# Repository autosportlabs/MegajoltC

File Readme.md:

Megajolt/C hardware and firmware

Project is incomplete. No support offered - github issues will be ignored. 

Please see LICENSE file for license details

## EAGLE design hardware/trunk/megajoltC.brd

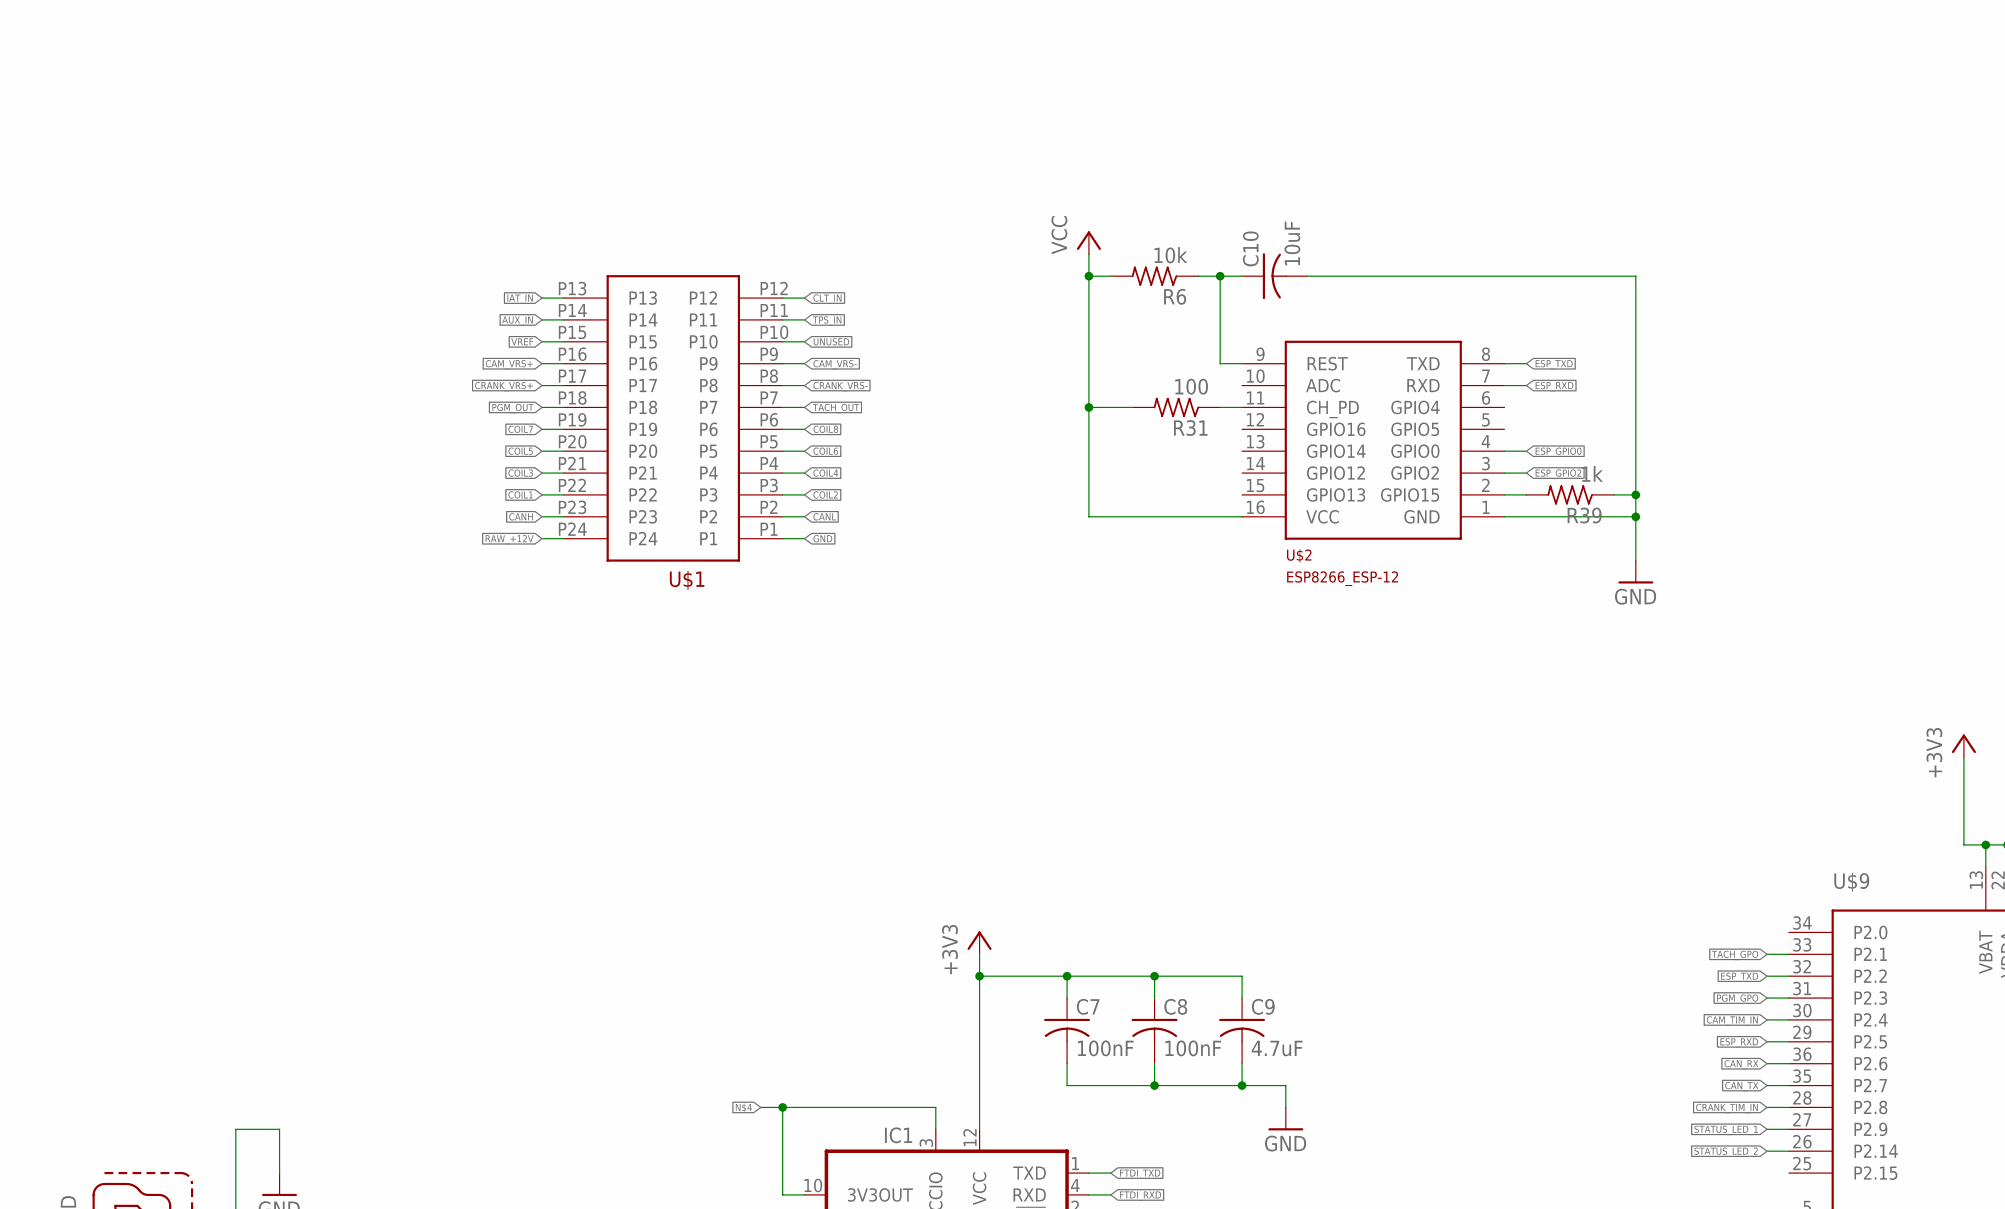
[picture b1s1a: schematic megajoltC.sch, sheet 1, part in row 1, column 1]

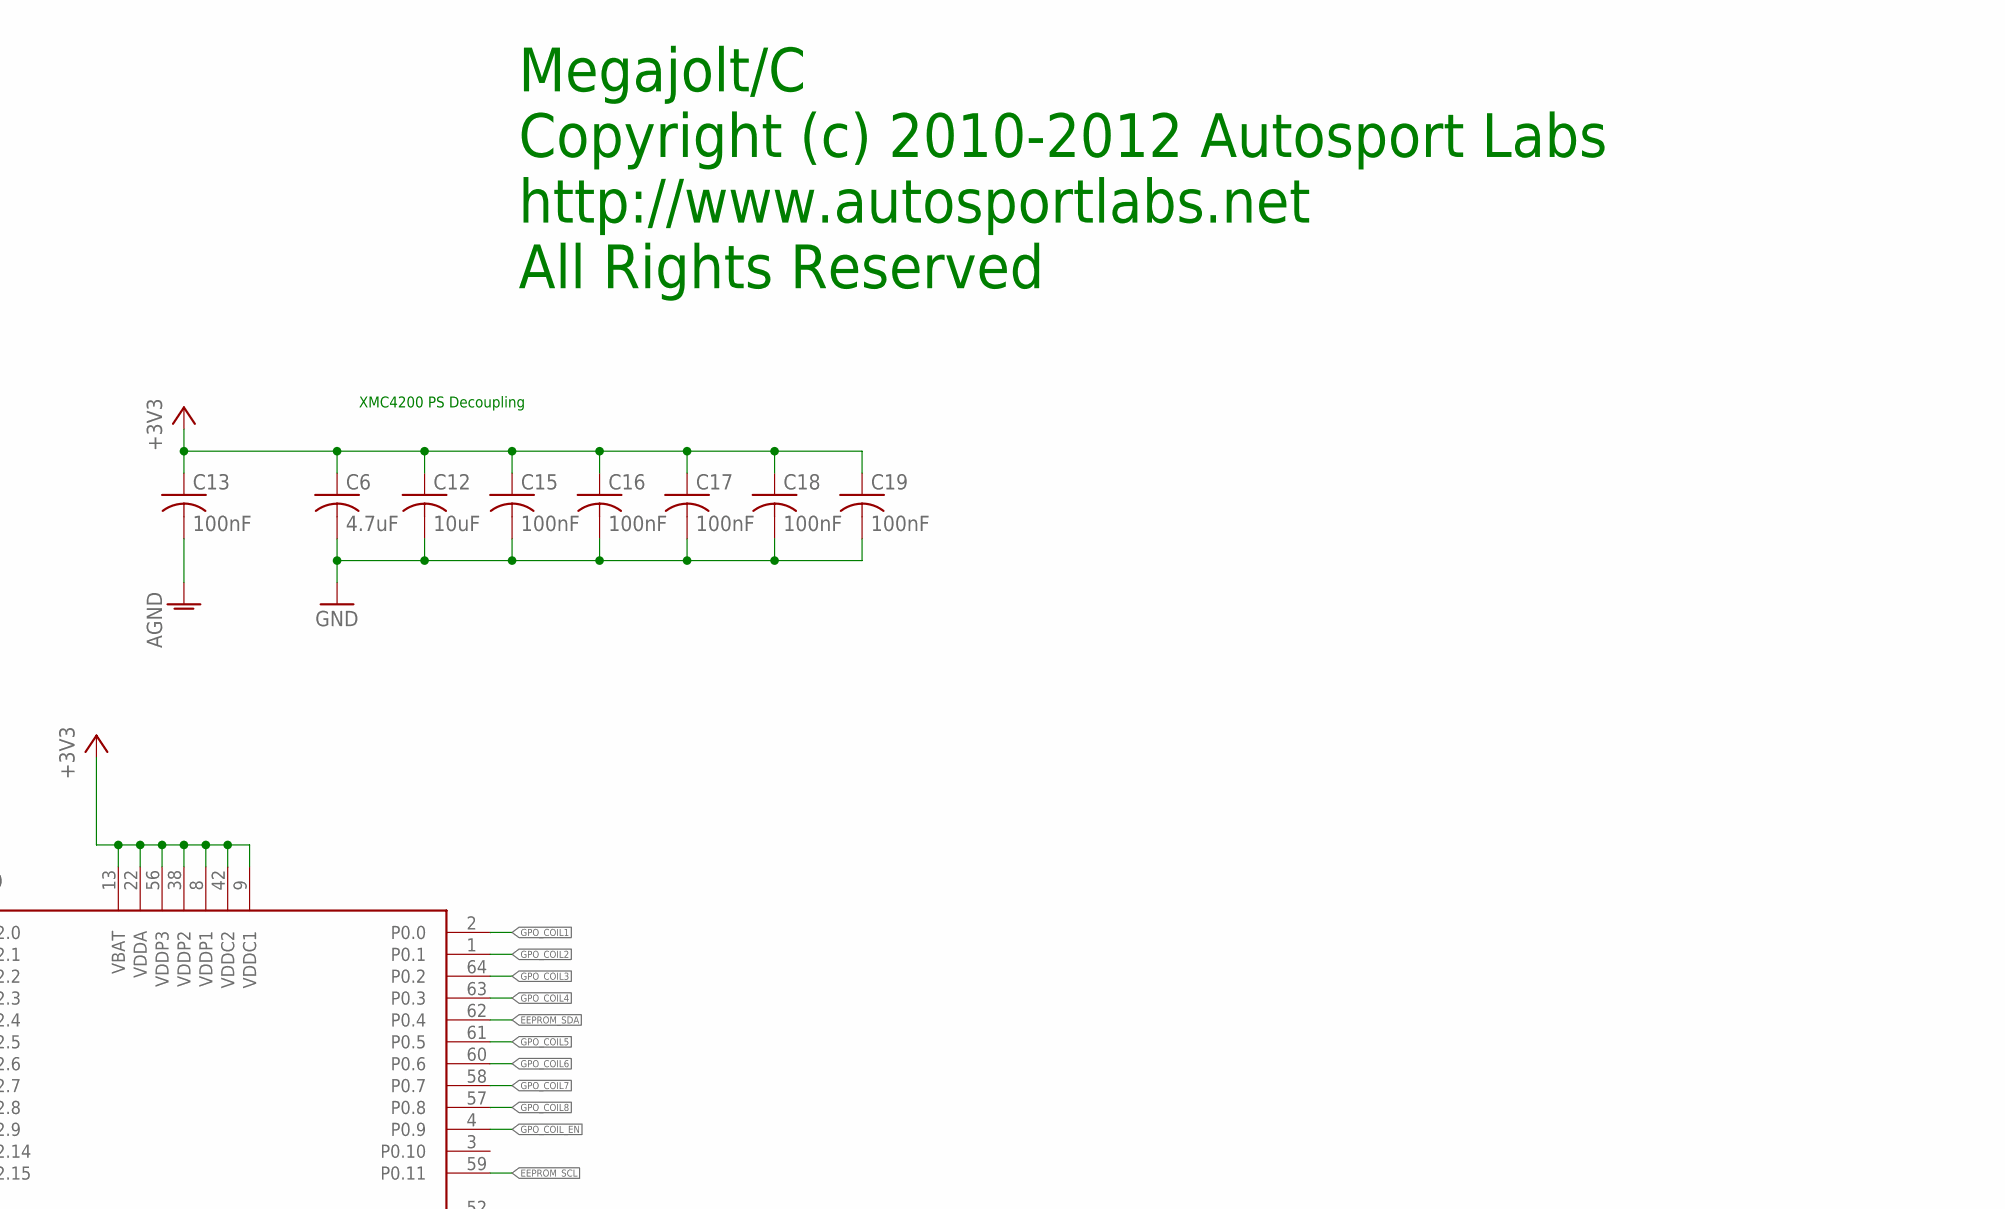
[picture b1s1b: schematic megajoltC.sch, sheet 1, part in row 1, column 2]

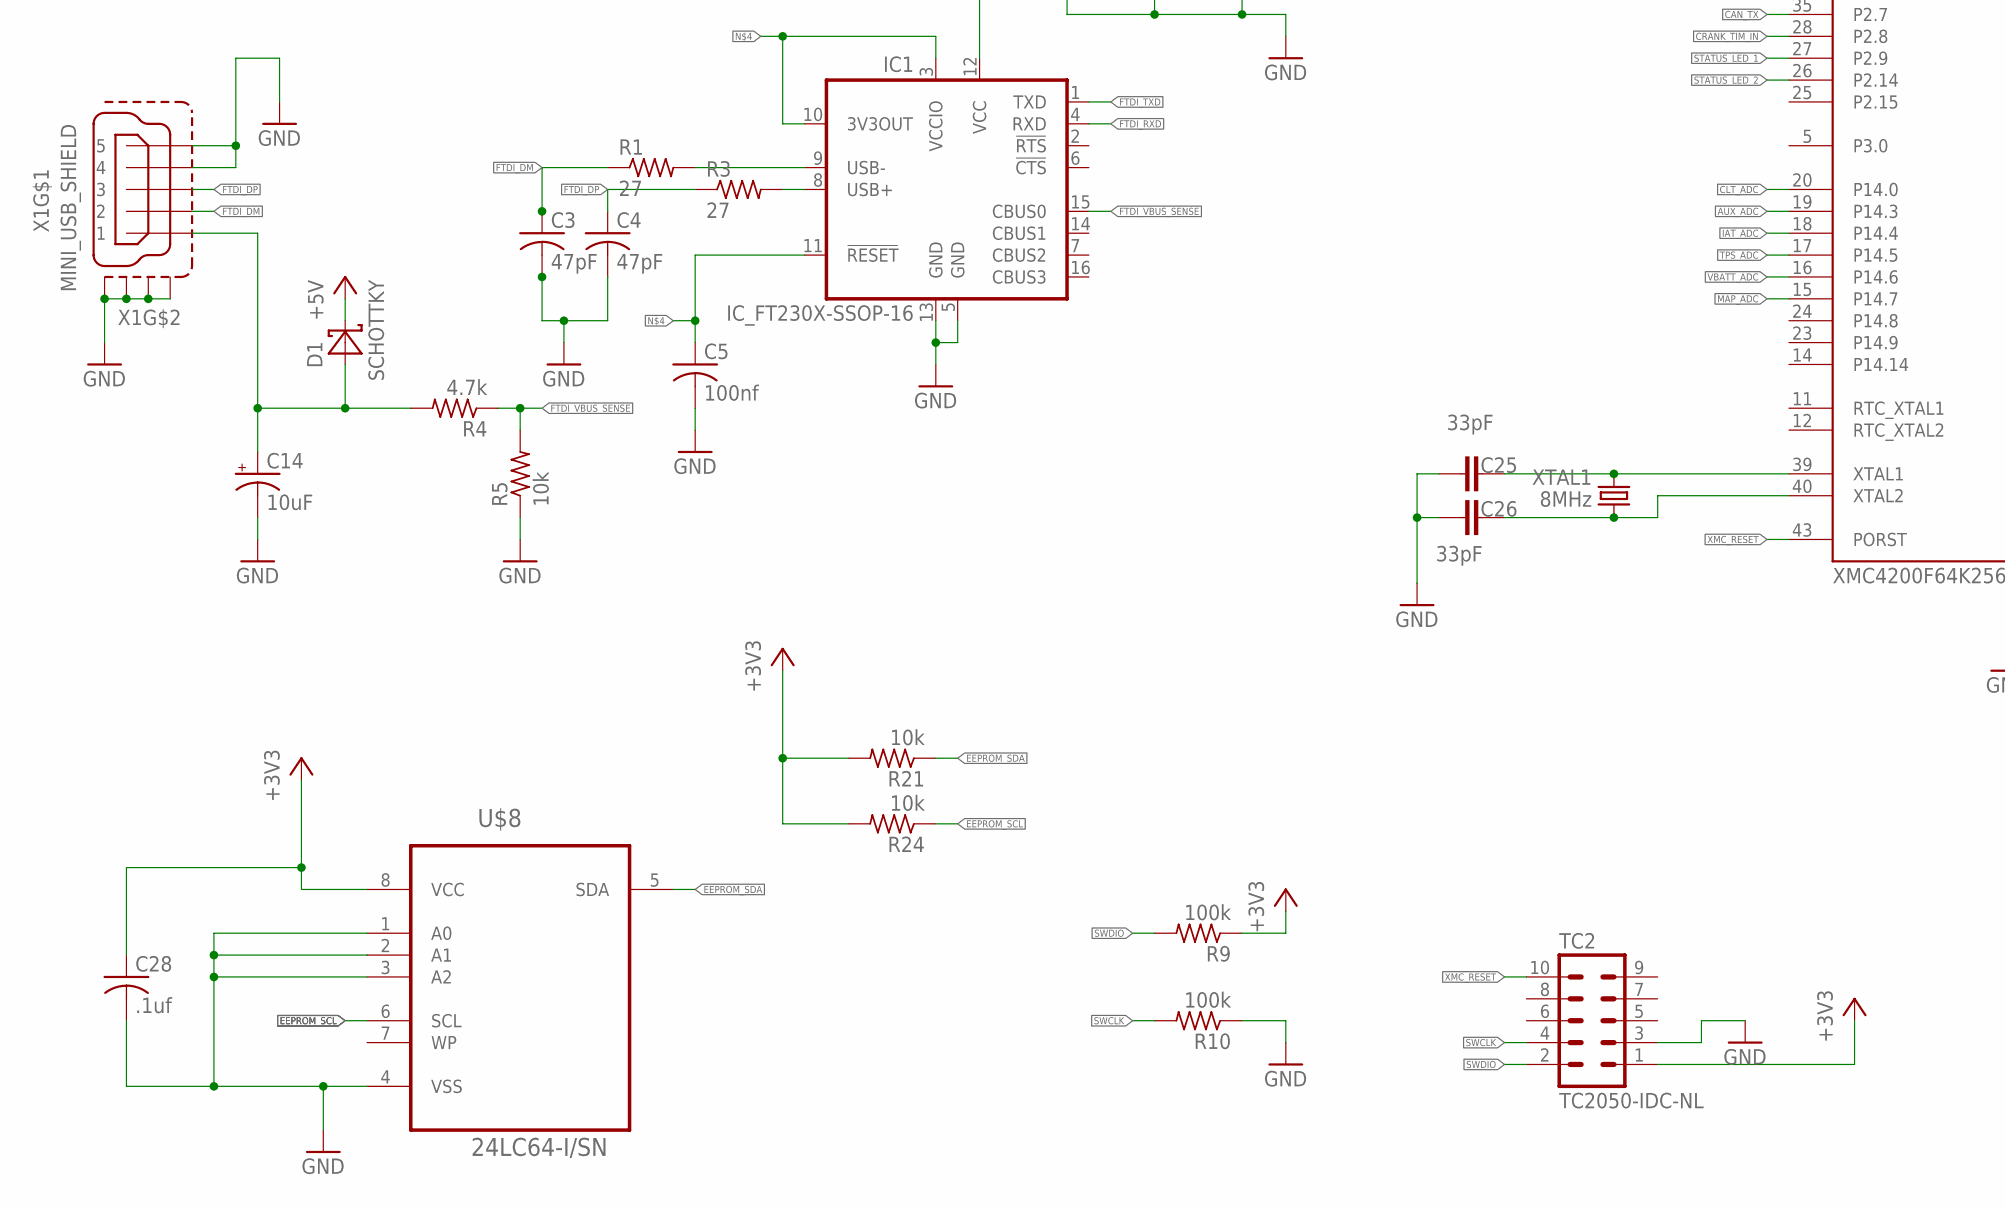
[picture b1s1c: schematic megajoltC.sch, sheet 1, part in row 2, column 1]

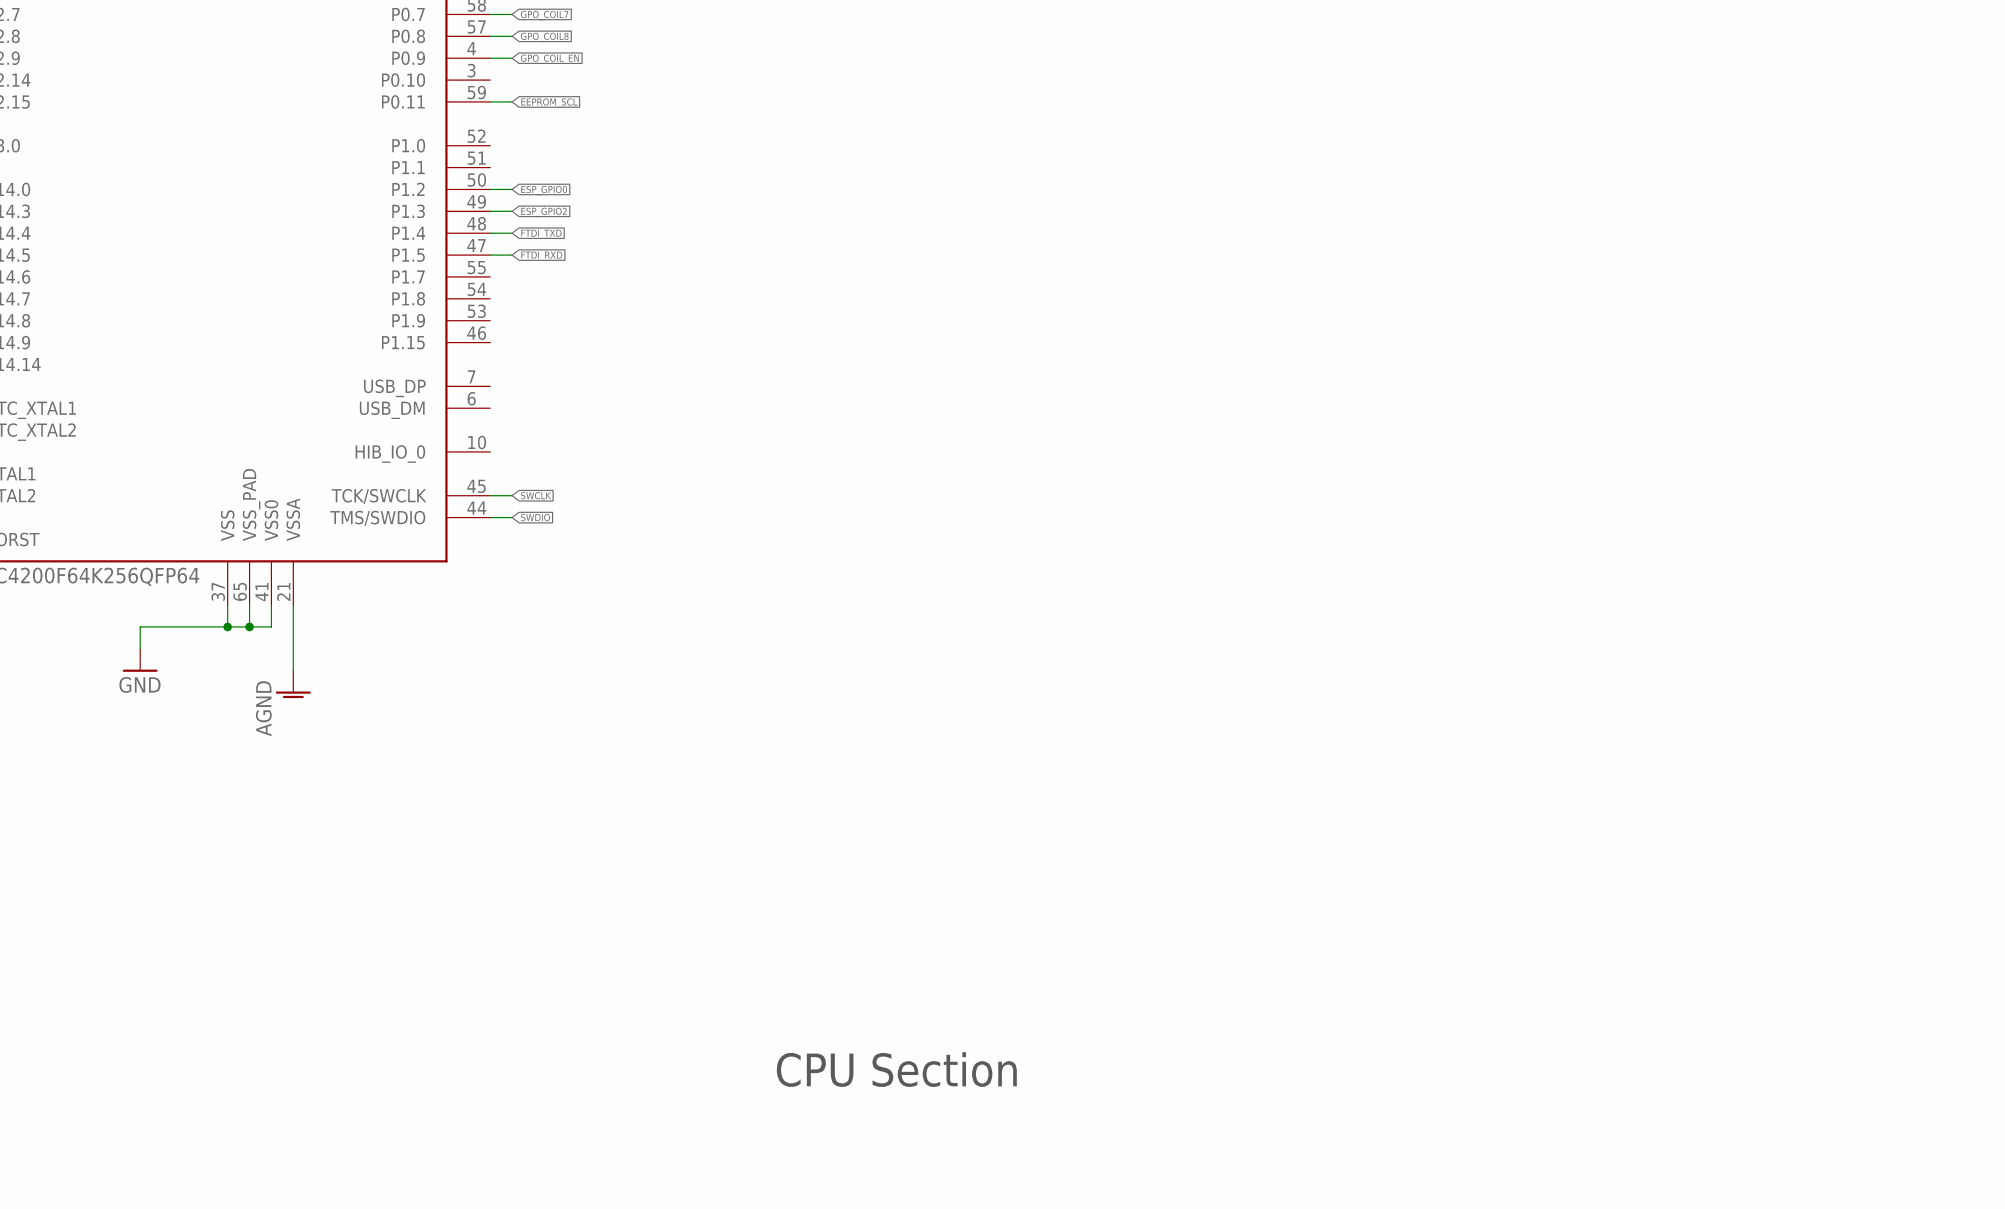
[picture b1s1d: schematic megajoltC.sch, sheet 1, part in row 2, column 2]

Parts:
C3, C4: 47pF; C0603
C5: 100nf; C0603
C6, C9: 4.7uF; C0603
C7, C8, C13, C15, C16, C17, C18, C19: 100nF; C0603
C10, C12: 10uF; C0603
C14: 10uF; SMC_A
C25, C26: 33pF; 0603
C28: .1uf; C0603
D1: SCHOTTKY; SMA
IC1: IC_FT230X-SSOP-16; SSOP-16-FTDI
R1, R3: 27; R0603
R4: 4.7k; R0603
R5, R6, R21, R24: 10k; R0603
R9, R10: 100k; R0603
R31: 100; R0603
R39: 1k; R0603
TC2: TC2050-IDC-NL
U$1: MOLEX_MINIFIT-JR-24
U$2: ESP8266_ESP-12; ESP8266-ESP12
U$8: 24LC64-I/SN; SOIC127P600X175-8N
U$9: XMC4200F64K256QFP64; INF-PG-LQFP-64-5800X5800T28
X1: MINI_USB_SHIELD; MINI-USB_JACK
XTAL1: 8MHz; CRYSTAL-SMD-5X3

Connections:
+3V3: C6.1, C7.1, C8.1, C9.1, C12.1, C13.1, C15.1, C16.1, C17.1, C18.1, C19.1, C28.1, IC1.12 (VCC), R9.1, R21.2, R24.2, TC2.1, U$8.8 (VCC), U$9.8 (VDDP1), U$9.9 (VDDC1), U$9.13 (VBAT), U$9.22 (VDDA), U$9.38 (VDDP2), U$9.42 (VDDC2), U$9.56 (VDDP3); also elsewhere on the board
+5V: D1.C; also elsewhere on the board
AGND: C13.2, U$9.21 (VSSA); also elsewhere on the board
AUX_ADC: U$9.19 (P14.3); also elsewhere on the board
AUX_IN: U$1.P14; also elsewhere on the board
CAM_TIM_IN: U$9.30 (P2.4); also elsewhere on the board
CAM_VRS+: U$1.P16; also elsewhere on the board
CAM_VRS-: U$1.P9; also elsewhere on the board
CANH: U$1.P23; also elsewhere on the board
CANL: U$1.P2; also elsewhere on the board
CAN_RX: U$9.36 (P2.6); also elsewhere on the board
CAN_TX: U$9.35 (P2.7); also elsewhere on the board
CLT_ADC: U$9.20 (P14.0); also elsewhere on the board
CLT_IN: U$1.P12; also elsewhere on the board
COIL1: U$1.P22; also elsewhere on the board
COIL2: U$1.P3; also elsewhere on the board
COIL3: U$1.P21; also elsewhere on the board
COIL4: U$1.P4; also elsewhere on the board
COIL5: U$1.P20; also elsewhere on the board
COIL6: U$1.P5; also elsewhere on the board
COIL7: U$1.P19; also elsewhere on the board
COIL8: U$1.P6; also elsewhere on the board
CRANK_TIM_IN: U$9.28 (P2.8); also elsewhere on the board
CRANK_VRS+: U$1.P17; also elsewhere on the board
CRANK_VRS-: U$1.P8; also elsewhere on the board
EEPROM_SCL: R24.1, U$8.6 (SCL), U$9.59 (P0.11)
EEPROM_SDA: R21.1, U$8.5 (SDA), U$9.62 (P0.4)
ESP_GPIO0: U$2.4 (GPIO0), U$9.50 (P1.2)
ESP_GPIO2: U$2.3 (GPIO2), U$9.49 (P1.3)
ESP_RXD: U$2.7 (RXD), U$9.29 (P2.5)
ESP_TXD: U$2.8 (TXD), U$9.32 (P2.2)
FTDI_DM: C3.1, R1.1, X1.2
FTDI_DP: C4.1, R3.1, X1.3
FTDI_RXD: IC1.4 (RXD), U$9.47 (P1.5)
FTDI_TXD: IC1.1 (TXD), U$9.48 (P1.4)
FTDI_VBUS_SENSE: IC1.15 (CBUS0), R4.1, R5.2
GND: C3.2, C4.2, C5.2, C6.2, C7.2, C8.2, C9.2, C10.2, C12.2, C14.-, C15.2, C16.2, C17.2, C18.2, C19.2, C25.1, C26.1, C28.2, IC1.5 (GND), IC1.13 (GND), R5.1, R10.1, R39.1, TC2.3, U$1.P1, U$2.1 (GND), U$8.1 (A0), U$8.2 (A1), U$8.3 (A2), U$8.4 (VSS), U$9.37 (VSS), U$9.41 (VSS0), U$9.65 (VSS_PAD), X1.4, X1.5, X1.M1 (S1), X1.M2 (S2), X1.M3 (S3), X1.M4 (S4); also elsewhere on the board
GPO_COIL1: U$9.2 (P0.0); also elsewhere on the board
GPO_COIL2: U$9.1 (P0.1); also elsewhere on the board
GPO_COIL3: U$9.64 (P0.2); also elsewhere on the board
GPO_COIL4: U$9.63 (P0.3); also elsewhere on the board
GPO_COIL5: U$9.61 (P0.5); also elsewhere on the board
GPO_COIL6: U$9.60 (P0.6); also elsewhere on the board
GPO_COIL7: U$9.58 (P0.7); also elsewhere on the board
GPO_COIL8: U$9.57 (P0.8); also elsewhere on the board
GPO_COIL_EN: U$9.4 (P0.9); also elsewhere on the board
IAT_ADC: U$9.18 (P14.4); also elsewhere on the board
IAT_IN: U$1.P13; also elsewhere on the board
MAP_ADC: U$9.15 (P14.7); also elsewhere on the board
unnamed: IC1.8 (USB+), R3.2
unnamed: IC1.9 (USB-), R1.2
unnamed: C5.1, IC1.3 (VCCIO), IC1.10 (3V3OUT), IC1.11 (!RESET)
unnamed: C10.1, R6.1, U$2.9 (REST)
unnamed: R31.1, U$2.11 (CH_PD)
unnamed: C26.2, U$9.40 (XTAL2), XTAL1.1
unnamed: R39.2, U$2.2 (GPIO15)
unnamed: C25.2, U$9.39 (XTAL1), XTAL1.3 (2)
PGM_GPO: U$9.31 (P2.3); also elsewhere on the board
PGM_OUT: U$1.P18; also elsewhere on the board
RAW_+12V: U$1.P24; also elsewhere on the board
STATUS_LED_1: U$9.27 (P2.9); also elsewhere on the board
STATUS_LED_2: U$9.26 (P2.14); also elsewhere on the board
SWCLK: R10.2, TC2.4, U$9.45 (TCK/SWCLK)
SWDIO: R9.2, TC2.2, U$9.44 (TMS/SWDIO)
TACH_GPO: U$9.33 (P2.1); also elsewhere on the board
TACH_OUT: U$1.P7; also elsewhere on the board
TPS_ADC: U$9.17 (P14.5); also elsewhere on the board
TPS_IN: U$1.P11; also elsewhere on the board
UNUSED: U$1.P10
VBATT_ADC: U$9.16 (P14.6); also elsewhere on the board
VBUS: C14.+, D1.A, R4.2, X1.1
VCC: R6.2, R31.2, U$2.16 (VCC); also elsewhere on the board
VREF: U$1.P15; also elsewhere on the board
XMC_RESET: TC2.10, U$9.43 (PORST)

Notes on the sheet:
Megajolt/C
Copyright (c) 2010-2012 Autosport Labs
http://www.autosportlabs.net
All Rights Reserved
CPU Section
XMC4200 PS Decoupling

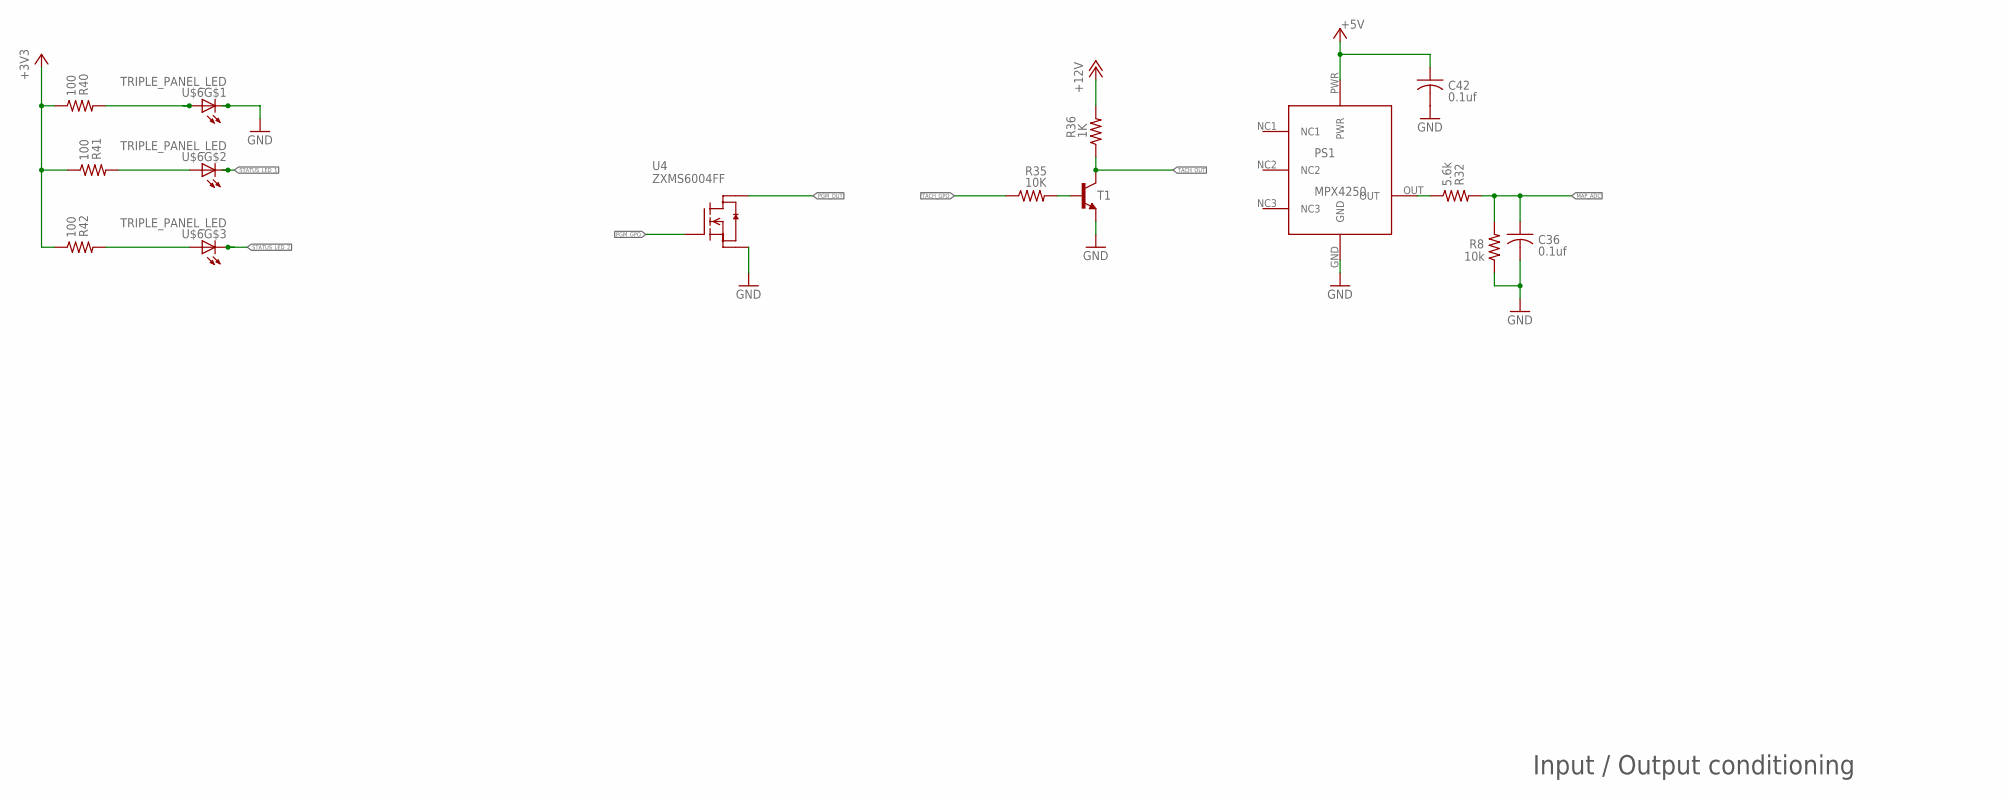
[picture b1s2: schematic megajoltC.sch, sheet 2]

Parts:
C36, C42: 0.1uf; C0603
PS1: MPX4250
R8: 10k; R0603
R32: 5.6k; R0603
R35: 10K; R0603
R36: 1K; R0603
R40, R41, R42: 100; R0603
T1: -NPN-SOT23-EBC; SOT23-EBC
U4: ZXMS6004FF; SOT-23
U$6: TRIPLE_PANEL_LED; RIGHT_ANGLE_3_LEDS_DEEP

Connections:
+3V3: R40.1, R41.1, R42.1; also elsewhere on the board
+5V: C42.1, PS1.PWR; also elsewhere on the board
GND: C36.2, C42.2, PS1.GND, R8.1, T1.E, U4.2 (S1), U$6.2 (C); also elsewhere on the board
MAP_ADC: C36.1, R8.2, R32.2; also elsewhere on the board
unnamed: PS1.OUT, R32.1
unnamed: R35.2, T1.B
unnamed: R40.2, U$6.1 (A)
unnamed: R41.2, U$6.3 (A)
unnamed: R42.2, U$6.5 (A)
NC1: PS1.NC1
NC2: PS1.NC2
NC3: PS1.NC3
PGM_GPO: U4.1 (G); also elsewhere on the board
PGM_OUT: U4.3 (D1); also elsewhere on the board
SAFE_+12V: R36.2; also elsewhere on the board
STATUS_LED_1: U$6.4 (C); also elsewhere on the board
STATUS_LED_2: U$6.6 (C); also elsewhere on the board
TACH_GPO: R35.1; also elsewhere on the board
TACH_OUT: R36.1, T1.C; also elsewhere on the board

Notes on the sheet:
Input / Output conditioning

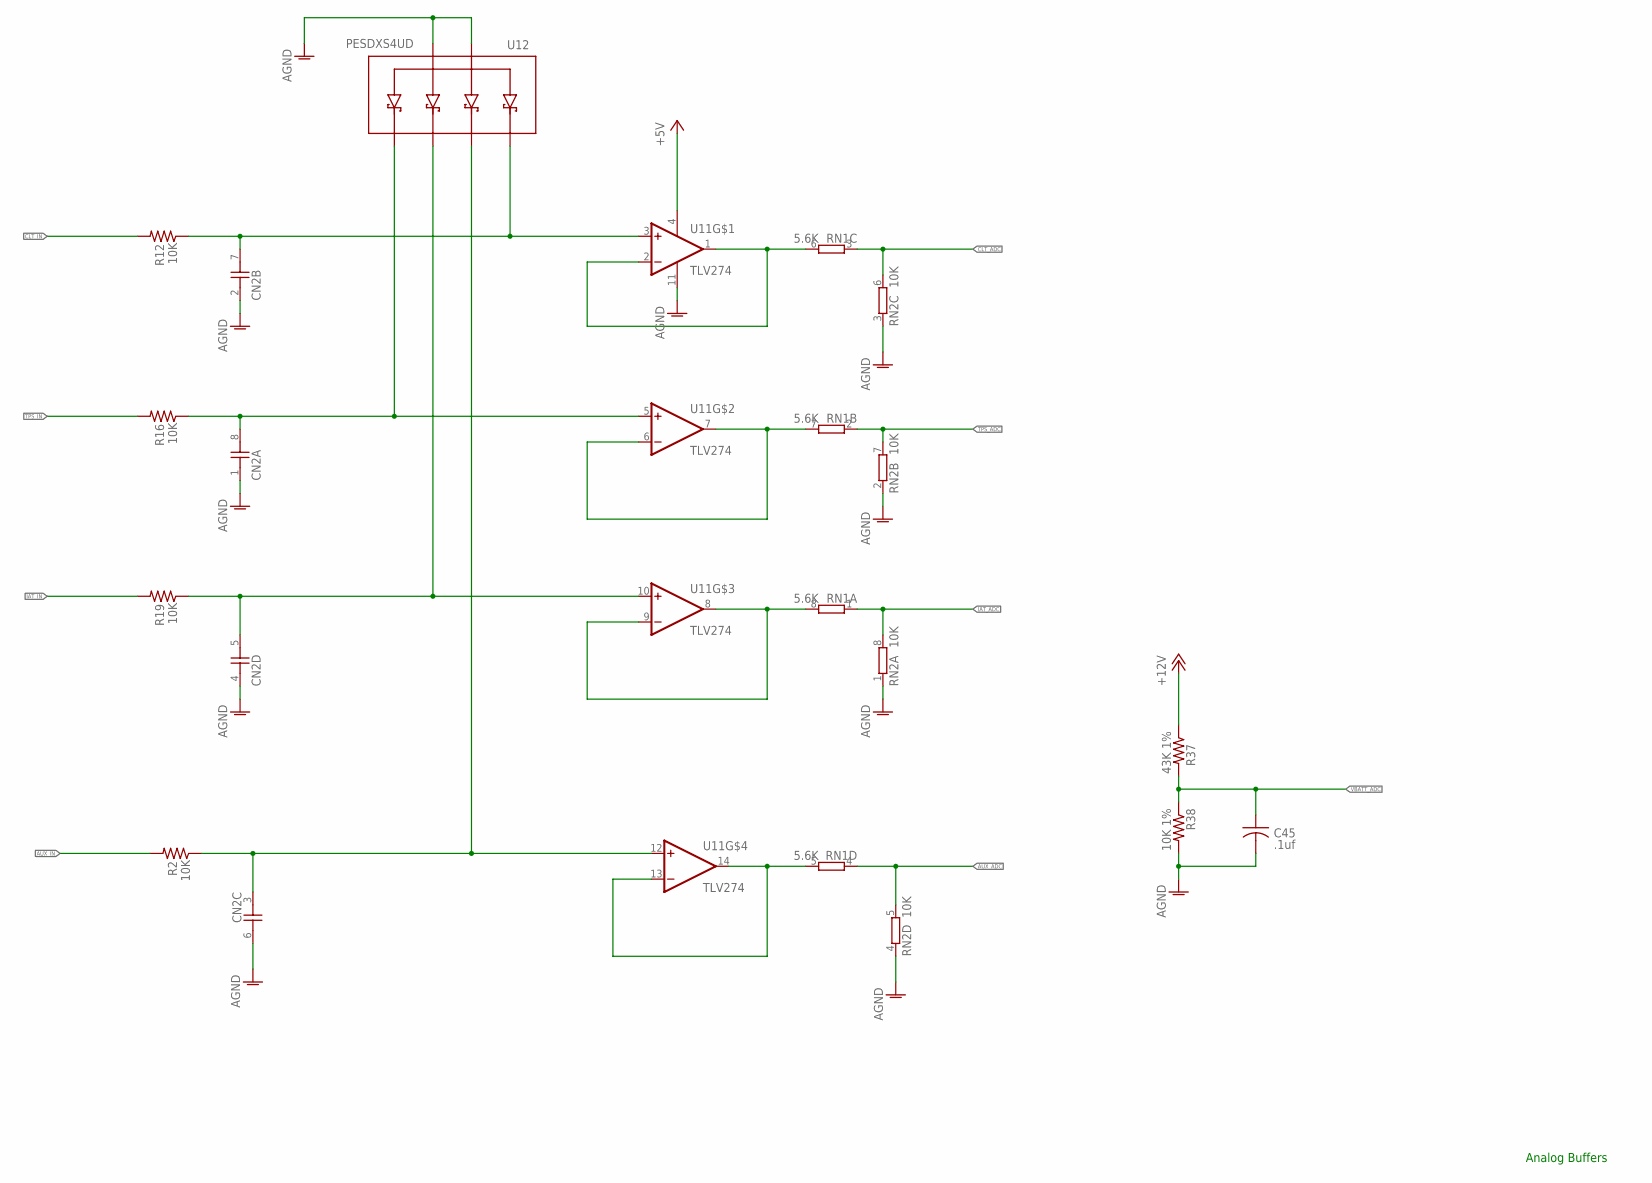
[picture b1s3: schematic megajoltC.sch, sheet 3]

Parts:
C45: .1uf; C0603
CN2: CAP_ARRAY_41206_ARRAY; 1206_ARRAY
R2, R12, R16, R19: 10K; R1206
R37: 43K 1%; R0603
R38: 10K 1%; R0603
RN1: 5.6K; 0603-ARC
RN2: 10K; 0603-ARC
U11: TLV274; SO14
U12: PESDXS4UD; SC-74

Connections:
+5V: U11.4 (V+); also elsewhere on the board
AGND: C45.2, CN2.1, CN2.2 (1), CN2.4 (1), CN2.6 (2), R38.2, RN2.1, RN2.2 (1), RN2.3 (1), RN2.4 (1), U11.11 (V-), U12.2, U12.5; also elsewhere on the board
ANALOG-FREQ_1_OPAMP_OUT1: RN1.6 (2), U11.1 (OUT), U11.2 (-IN)
ANALOG-FREQ_1_OPAMP_OUT2: RN1.7 (2), U11.6 (-IN), U11.7 (OUT)
ANALOG-FREQ_1_OPAMP_OUT3: RN1.8 (2), U11.8 (OUT), U11.9 (-IN)
AUX_ADC: RN1.4 (1), RN2.5 (2); also elsewhere on the board
AUX_IN: R2.2; also elsewhere on the board
CLT_ADC: RN1.3 (1), RN2.6 (2); also elsewhere on the board
CLT_IN: R12.2; also elsewhere on the board
IAT_ADC: RN1.1, RN2.8 (2); also elsewhere on the board
IAT_IN: R19.2; also elsewhere on the board
unnamed: RN1.5 (2), U11.13 (-IN), U11.14 (OUT)
unnamed: CN2.7 (2), R12.1, U11.3 (+IN), U12.1
unnamed: CN2.8 (2), R16.1, U11.5 (+IN), U12.6
unnamed: CN2.5 (2), R19.1, U11.10 (+IN), U12.4
unnamed: CN2.3 (1), R2.1, U11.12 (+IN), U12.3
SAFE_+12V: R37.1; also elsewhere on the board
TPS_ADC: RN1.2 (1), RN2.7 (2); also elsewhere on the board
TPS_IN: R16.2; also elsewhere on the board
VBATT_ADC: C45.1, R37.2, R38.1; also elsewhere on the board

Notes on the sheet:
Analog Buffers

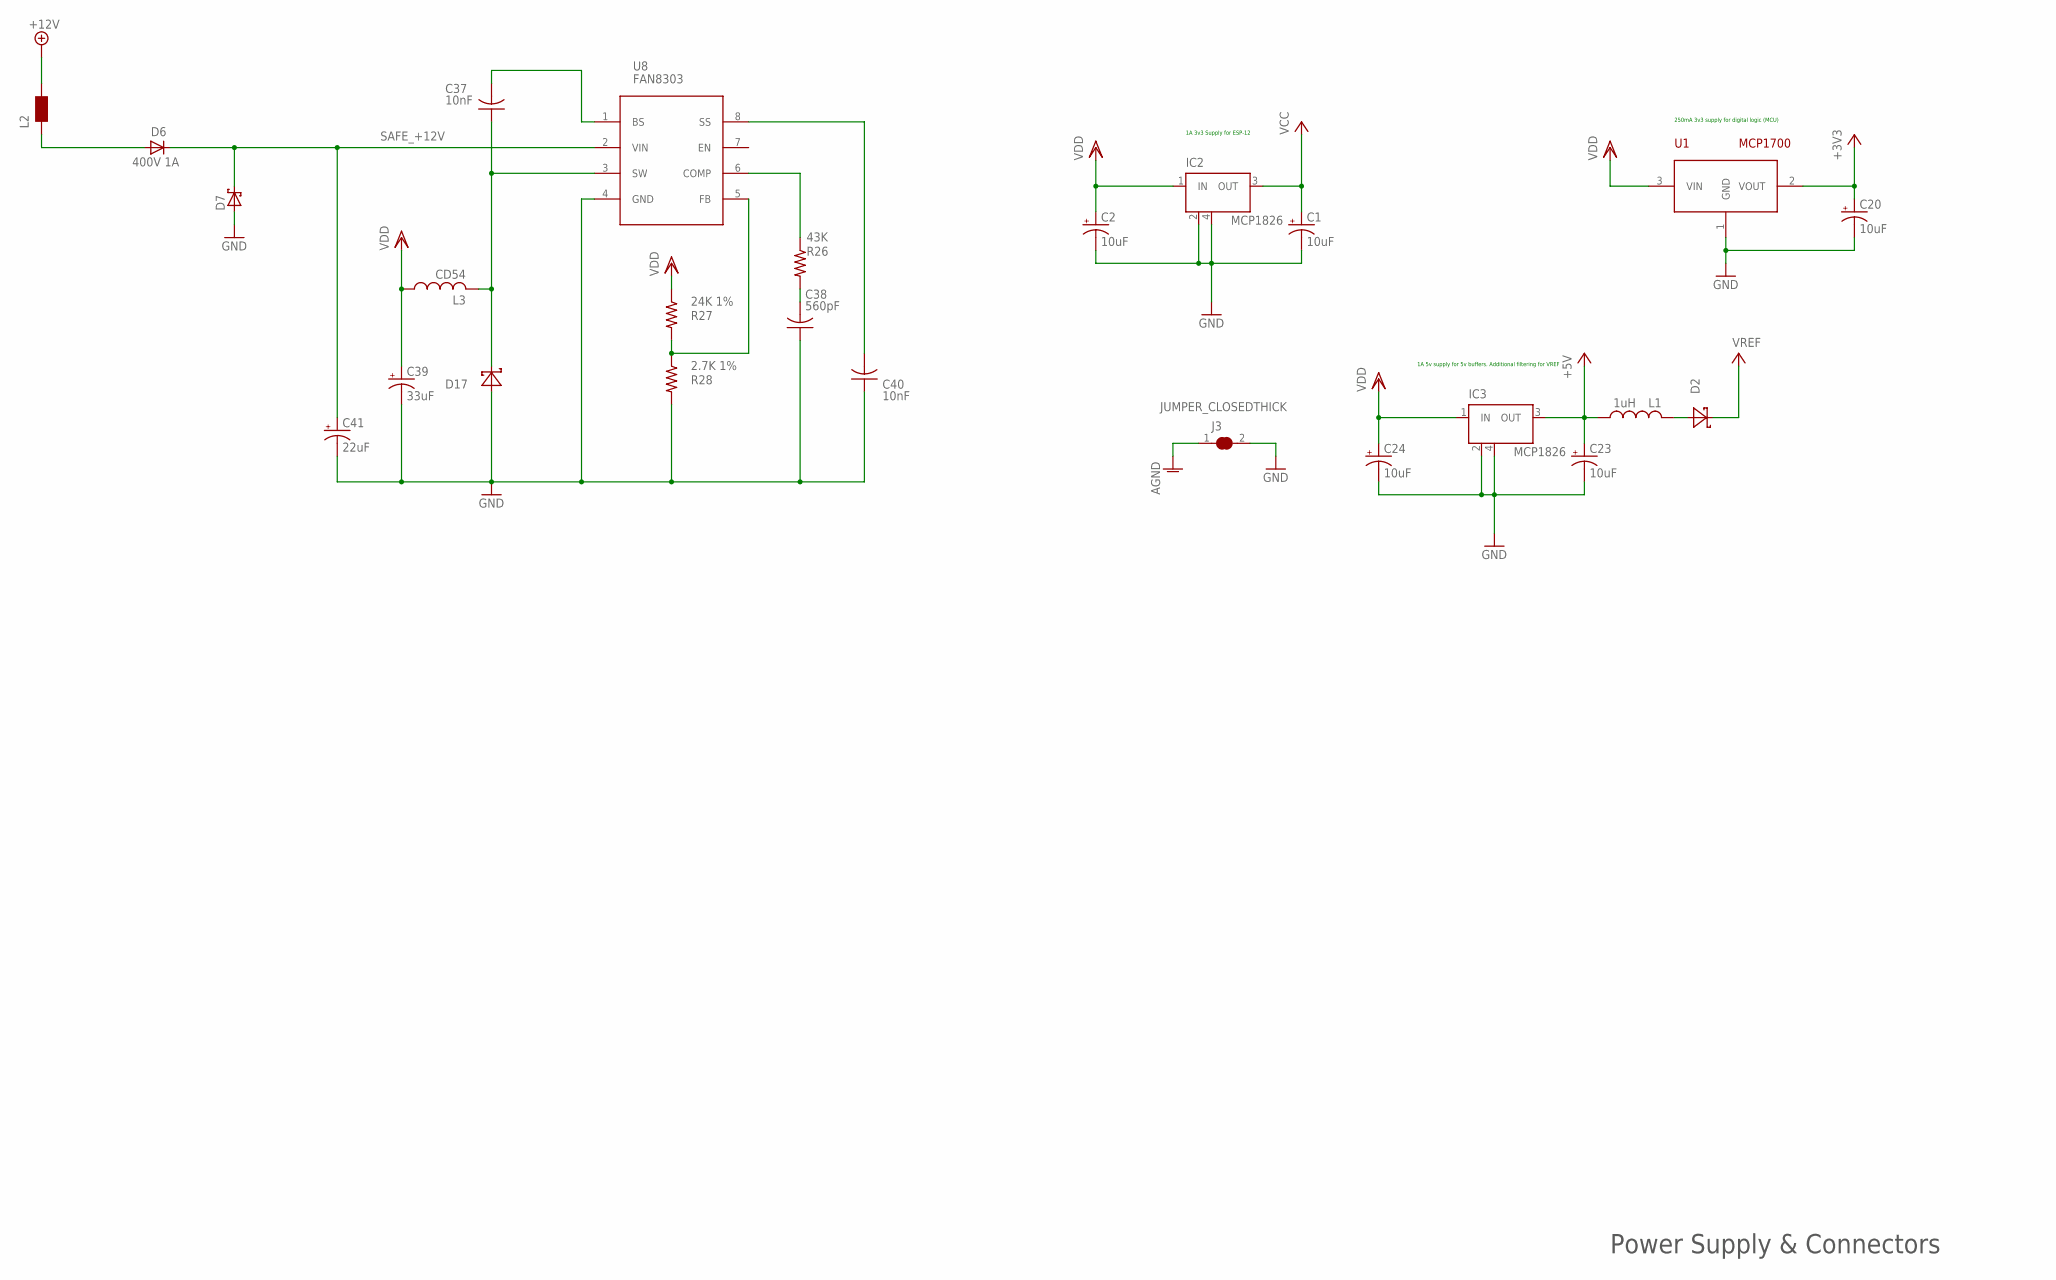
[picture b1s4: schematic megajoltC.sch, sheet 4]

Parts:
C1, C2, C20, C23, C24: 10uF; SMC_A
C37, C40: 10nF; C0603
C38: 560pF; C0603
C39: 33uF; SMC_D
C41: 22uF; 153CLV-0605
D2, D17: SCHOTTKY; SMA
D6: 400V 1A; SMA
D7: SCHOTTKY-DIODESMC; SMC
IC2, IC3: MCP1826; SOT223
J3: JUMPER_CLOSEDTHICK; JUMPER_CLOSED_THICK
L1: 1uH; 1210
L2: WE-CBF_1812; 1812
L3: CD54
R26: 43K; R0603
R27: 24K 1%; R0603
R28: 2.7K 1%; R0603
U1: MCP1700; SOT-23
U8: FAN8303; SO-8

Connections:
+3V3: C20.+, U1.2 (VOUT); also elsewhere on the board
+5V: C23.+, IC3.3 (OUT), L1.1; also elsewhere on the board
AGND: J3.1; also elsewhere on the board
GND: C1.-, C2.-, C20.-, C23.-, C24.-, C38.1, C39.-, C40.1, C41.-, D7.A, D17.A, IC2.2 (GND), IC2.4 (GND), IC3.2 (GND), IC3.4 (GND), J3.2, R28.2, U1.1 (GND), U8.4 (GND); also elsewhere on the board
unnamed: D2.A, L1.2
unnamed: R27.2, R28.1, U8.5 (FB)
unnamed: C37.2, U8.1 (BS)
unnamed: C37.1, D17.C, L3.P$2 (2), U8.3 (SW)
unnamed: C38.2, R26.2
unnamed: R26.1, U8.6 (COMP)
unnamed: C40.2, U8.8 (SS)
unnamed: D6.A, L2.1
RAW_+12V: L2.2; also elsewhere on the board
SAFE_+12V: C41.+, D6.C, D7.C, U8.2 (VIN); also elsewhere on the board
VCC: C1.+, IC2.3 (OUT); also elsewhere on the board
VDD: C2.+, C24.+, C39.+, IC2.1 (IN), IC3.1 (IN), L3.P$1 (1), R27.1, U1.3 (VIN)
VREF: D2.C; also elsewhere on the board

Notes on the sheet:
Power Supply & Connectors
1A 3v3 Supply for ESP-12
1A 5v supply for 5v buffers. Additional filtering for VREF
250mA 3v3 supply for digital logic (MCU)

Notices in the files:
hardware/trunk/megajoltC.brd:
Copyright 2010-2015 Autosport Labs - All Rights Reserved
